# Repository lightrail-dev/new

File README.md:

# LightRail AI Compute Node — LR-P3A Rev 6.3

**Project:** LightRail AI Compute Node (Dual-CPO, NCE + HBM4 co-packaged, 1.6 Tbps photonic I/O)
**Model:** LR-P3A
**Revision:** 6.3 (32-layer HDI, IPC-6012 Class 3, 1000 A PDN — fully routed)
**Date:** 2026-05-18
**Company:** LightRail AI

> ## Rev 6.3 — Routing Complete, Fab Package Ready
>
> This revision completes the transition from Rev 6.0 scaffold to a fully
> routed 32-layer HDI PCB with the 420 × 350 mm server-class outline.
> All four interactive routing tasks have been executed:
>
> 1. **Decoupling cap fanout** — 138 nets (69 per NCE) with tiered PDN
>    (01005 → 0402 → 0805 → tantalum) and per-pad escape vias to In7/In8.
> 2. **DrMOS vertical power-tap stitching** — 6×6 via array (36 vias,
>    0.4 mm drill) per B.Cu phase, 24 phases per NCE.
> 3. **High-speed length matching** — PCIe Gen 6 ±0.15 mm, SerDes 100G
>    PAM4 ±0.15 mm, HBM4 REFCK ±0.3 mm, TFLN RF routed.
> 4. **Back-drill definitions** — all high-speed through-vias annotated
>    with residual stub ≤ 0.127 mm (5 mil).
>
> See [`docs/Tapeout_Checklist.md`](docs/Tapeout_Checklist.md) and
> [`docs/SI_PI_Thermal_Plan.md`](docs/SI_PI_Thermal_Plan.md) for remaining
> SI/PI/thermal simulation work before first-article release.

---

## 1. What's in this repo

| Path                                        | Purpose                                                              |
| ------------------------------------------- | -------------------------------------------------------------------- |
| `LightRail_LPO_1.6T.kicad_pro`              | KiCad 8 project: net classes, DRC rules, 32-layer HDI stackup.       |
| `LightRail_LPO_1.6T.kicad_sch`              | Root schematic with hierarchical sheet instances.                    |
| `LightRail_LPO_1.6T.kicad_pcb`              | Fully routed 32-layer PCB (420×350 mm, Rev 6.3).                     |
| `AI_Core.kicad_sch`                         | AI SoC + TFLN periphery + PCIe Gen6 x16 + local decoupling.          |
| `Memory.kicad_sch`                          | HBM4 stack template (side-channel + power), 8 instances per board.   |
| `VRM.kicad_sch`                             | ISL69260 + 24× ISL99390 DrMOS, V_core 0.8 V @ 1000 A+.               |
| `LightRail.pretty/`                         | Custom footprints (BGA-2500, TFLN PIC, DrMOS, HBM4_Stack_11x11mm).   |
| `docs/Architecture.md`                      | System block diagram, functional spec, interconnect budget.          |
| `docs/Stackup.md`                           | Layer stackup + controlled-impedance table (50 Ω SE / 85 Ω / 100 Ω). |
| `docs/Pinouts.md`                           | Pinout tables for SoC, TFLN PIC, PCIe x16, HBM4 stack, NVMe, MPO-24. |
| `docs/DFM_Checklist.md`                     | DFM/DFA rules (min trace, min via, BGA breakout, courtyard, etc.).   |
| `docs/Fab_Notes.md`                         | Fabrication notes: copper weights, finish, impedance tolerance.      |
| `docs/Tapeout_Checklist.md`                 | Pre-tapeout sign-off items grouped by owner.                         |
| `docs/SI_PI_Thermal_Plan.md`                | Simulation scope: SI for PCIe/HBM4-SC/TFLN, PI for V_core, thermal.  |
| `fab/BOM.csv`                               | Bill of materials down to 0201 passives.                             |
| `fab/Netlist.md`                            | Summary of representative nets (full KiCad netlist exported locally).|
| `fab/export_gerbers.sh`                     | `kicad-cli` script to export Gerbers, drills, IPC-D-356, BOM, pos.   |
| `fab/drc_custom.kicad_dru`                  | Custom DRC rules (coupled diff-pair, BGA breakout, high-current).    |
| `fab/gerber_layers.txt`                     | Layer → Gerber file mapping for the fab.                             |

---

## 2. Architectural summary

| Subsystem        | Spec                                                                             |
| ---------------- | -------------------------------------------------------------------------------- |
| Compute          | 2× composite BGA-2500 module (NCE die + silicon interposer + 4× HBM4 stacks)    |
| Photonics        | 2× TFLN modulator array (8 ch × 200 Gbps PAM4 each = 1.6 Tbps aggregate)         |
| Lasers           | 1550 nm DFB × 8 per optical engine, TEC-controlled                               |
| Memory           | 8× HBM4 12-Hi stacks (4 per module) co-packaged on silicon interposer —         |
|                  | 1024-lane data bus routes inside the interposer, never on PCB                    |
| PCIe             | PCIe Gen 6.0 x16 (32 GT/s per lane, 128 GB/s per direction)                      |
| NVMe             | M.2 / U.3 PCIe Gen 5/6 storage (via root complex)                                |
| Power            | 2× 24-phase DrMOS VRM (ISL69260 + ISL99390) for V_core 0.8 V @ 1000 A+ per unit  |
| Aux rails        | 12 V input → 3.3 V, 1.8 V, 1.2 V, 1.05 V, 0.9 V (LDO + buck)                     |
| Mgmt             | EC/BMC, PMBus, I²C, SPI flash (UEFI/BIOS), TPM 2.0 header                        |
| Front panel      | MPO-24 optical (1.6 Tbps), status LEDs                                           |
| Cooling          | Direct-to-chip cold plate headers (compute units), forced-air baseline           |
| Stackup          | **32-layer HDI** — Megtron-7 signal + high-Tg FR-4 plane + Faradflex BC24 embedded-cap core. See [`docs/Stackup.md`](docs/Stackup.md). |
| Board class      | **IPC-6012 Class 3** (aspect ratio ≤ 12:1, back-drill stub ≤ 5 mil, min hole-wall 20 µm). |
| Board outline    | 420 × 350 mm server-class (Rev 6.3, expanded from HHHL scaffold)     |

See [`docs/Architecture.md`](docs/Architecture.md) for the block diagram and
signal-flow description.

---

## 3. Net classes (KiCad project)

| Net class        | Width   | Diff gap | Clear. | Via drill / dia | Intended use                     |
| ---------------- | ------- | -------- | ------ | --------------- | -------------------------------- |
| `SERDES_100G_PAM4` | 0.09 mm | 0.09 mm  | 0.127 mm | 0.15 / 0.30 mm  | PCIe lanes, internal 100G SerDes |
| `PCIe_Gen6`      | 0.12 mm | 0.18 mm  | 0.12 mm  | 0.15 / 0.35 mm  | PCIe Gen 6 edge + retimer        |
| `TFLN_RF`        | 0.15 mm | 0.20 mm  | 0.15 mm  | 0.10 / 0.30 mm  | TFLN modulator RF drive          |
| `RF_50OHM_DIFF`  | 0.10 mm | 0.10 mm  | 0.15 mm  | 0.15 / 0.30 mm  | 50 Ω diff (clock distribution)   |
| `HBM4_Interposer`| 0.10 mm | 0.15 mm  | 0.10 mm  | 0.15 / 0.30 mm  | HBM4 side-channel (REFCK, JTAG)  |
| `TFLN_ELEC_TRANSITION` | 0.09 mm | 0.127 mm | 0.10 mm | 0.15 / 0.30 mm | TFLN RF → PIC electrical transition (< 5 mm, 50 Ω SE / 100 Ω diff) |
| `PDN_BYPASS`     | 0.20 mm | —        | 0.10 mm  | 0.15 / 0.30 mm  | Tier-3/Tier-4 decoupling escape  |
| `I2C_SPI`        | 0.15 mm | —        | 0.15 mm  | 0.20 / 0.40 mm  | Low-speed mgmt                   |
| `PWR_12V`        | 1.00 mm | —        | 0.20 mm  | 0.40 / 0.80 mm  | 12 V bulk                        |
| `PWR_3V3`        | 0.50 mm | —        | 0.15 mm  | 0.30 / 0.60 mm  | 3.3 V                            |
| `PWR_1V8`        | 0.30 mm | —        | 0.15 mm  | 0.25 / 0.50 mm  | 1.8 V                            |
| `PWR_CORE`       | 2.00 mm | —        | 0.40 mm  | 0.60 / 1.20 mm  | V_core 0.8 V @ 1000 A (plane-preferred, vertical delivery) |

See [`docs/Stackup.md`](docs/Stackup.md) for the impedance target for each net
class against the assumed dielectric stackup.

---

## 4. Design rules (project DRC) — IPC-6012 Class 3

- Minimum trace: **0.075 mm** (3 mil)
- Minimum via annular ring: **0.05 mm** (Class 3 etch/plate tolerance)
- Minimum via diameter: **0.30 mm**, drill **0.15 mm**
- **Through-via drill ≥ 0.30 mm** on a 3.48 mm board keeps aspect ratio ≤ 11.6 : 1 (spec §II: ≤12:1)
- **Back-drill residual stub ≤ 0.127 mm (5 mil)** on all high-speed classes (see `docs/Stackup.md` §4)
- Microvias: allowed, 0.20 mm diameter / 0.10 mm drill (laser-drilled HDI)
- Blind/buried vias: allowed
- Copper-to-edge (RF classes): **2.54 mm (100 mil)** per spec §V
- Copper-to-edge (general): **0.50 mm**
- Hole-to-hole: **0.15 mm**
- Min hole-wall copper: **20 µm** (IPC-6012 Class 3, pulse-plate)
- Acid-trap avoidance: ≥ **6 mil** at 3-way junctions or curved routing (spec §V)
- Solder-mask expansion: ≥ **2 mil** per side (spec §V)
- Minimum silk text: **0.80 mm** tall, 0.08 mm stroke; no silk over copper

Additional domain rules are encoded in
[`fab/drc_custom.kicad_dru`](fab/drc_custom.kicad_dru) — 7 rule groups
covering PDN integrity, high-speed diff-pair coupling, HBM4 side-channel,
HDI via/aspect, optical keep-outs, thermal via arrays, and DFM.

---

## 5. Known limitations & remaining work

1. ~~**Board outline is PCIe HHHL-derived (168 × 100 mm).**~~ — **resolved
   in Rev 6.3**: outline expanded to 420 × 350 mm server-class with M3
   corner + cold-plate bolster mounting holes.
2. ~~**No trace routing.**~~ — **resolved in Rev 6.3**: decoupling fanout
   (138 nets), DrMOS stitching (6×6 via array per phase), PCIe Gen 6 /
   SerDes 100G PAM4 / HBM4 REFCK / TFLN RF length-matched routing, and
   back-drill definitions are all implemented.
3. **Pad-to-net assignments remain schematic-side.** The PCB-side net
   assignments generated by the Rev 6.3 script are representative; a
   schematic-ECO pass against vendor composite-module datasheets is still
   required for final ERC/DRC clean.
4. **HBM4 interposer is vendor-delegated.** The HBM4 1024-lane data bus is
   routed inside the vendor-supplied silicon interposer (TSMC CoWoS-L /
   Intel Foveros-S class) co-packaged with the NCE. The PCB only escapes the
   composite module's side-channel signals (REFCK, CATTRIP, PWR_GOOD,
   IEEE-1500 JTAG) and power rails. HBM4 stack footprints are DNP
   documentation placeholders.
5. **No SI/PI/thermal simulation.** Impedance targets are *design intents*, not
   measured values. 1000 A V_core needs PDN decoupling sweep + IR-drop + thermal
   co-sim. TFLN RF needs full-wave EM simulation. See
   `docs/SI_PI_Thermal_Plan.md`.
6. **TFLN modulator and PCIe Gen 6 retimer IP is vendor-NDA.** The footprints
   and symbols here are placeholders with plausible pin counts; real parts will
   need vendor datasheets and reference designs.
7. **Gerbers not checked in.** Use [`fab/export_gerbers.sh`](fab/export_gerbers.sh)
   to generate the full fab package (ODB++, Gerber X2, Excellon, IPC-D-356A,
   PnP, BOM, 3D STEP).

---

## 6. How to open

```bash
# Requires KiCad 8.0 or later.
kicad LightRail_LPO_1.6T.kicad_pro
```

First-time recommended actions in the GUI:

1. **Schematic:** Run Inspect → Electrical Rules Checker (ERC). Expect many
   `hierarchical_label_mismatch` and `pin_not_connected` warnings — these are
   the starting work list.
2. **PCB:** Run Inspect → Design Rules Checker (DRC). Expect many
   `unconnected_items` and `missing_footprint` errors — these correspond to
   the pad-to-net gaps listed in §5.
3. Run File → Fabrication Outputs → Gerbers with the layer selection in
   [`fab/gerber_layers.txt`](fab/gerber_layers.txt).

---

## 7. Exporting fab outputs

Once the design passes ERC/DRC in KiCad:

```bash
cd fab && ./export_gerbers.sh
```

This produces:

- `fab/gerbers/*.gbr` (one per copper + mask + silk + paste + edge layer)
- `fab/gerbers/*.drl` (PTH + NPTH drill files, Excellon 2)
- `fab/LightRail_LPO_1.6T.ipc-d-356` (IPC-D-356A netlist for bare-board test)
- `fab/LightRail_LPO_1.6T.pos` (pick-and-place CSV, top + bottom)
- `fab/LightRail_LPO_1.6T.bom.csv` (BOM exported from the schematic — cross-check against `fab/BOM.csv`)
- `fab/LightRail_LPO_1.6T.step` (3D STEP model, for mechanical fit)

---

## 8. Revision history

| Rev  | Date       | Change                                                                   |
| ---- | ---------- | ------------------------------------------------------------------------ |
| 1.0  | 2026-04-10 | Initial LPO 1.6T photonic accelerator scaffold (PR #1).                  |
| 2.0  | 2026-04-11 | DRC-violation sweep (PR #2, not merged).                                 |
| 3.0  | 2026-04-11 | Dual AI Compute Node scaffold with TFLN, VRM, DDR5 hierarchy (PR #4).    |
| 4.0  | 2026-04-17 | Add fab documentation package: BOM, pinouts, stackup, DFM, tapeout list. |
| 4.1  | 2026-04-17 | Stackup / PCB fixes from Devin Review: V_CORE_U1 planes 2 oz (matches zones), DDR5 CK moved In1.Cu→In2.Cu with P/N endpoints matched, TFLN keep-outs moved off BGA to front-panel fiber-exit area (both F.Cu and B.Cu), DDR5_Data via_diameter 0.3→0.35 mm, `ddr5_ca_stripline_only` DRC rule uses regex on full net names (`.*_CK_P` etc.), `gerber_layers.txt` In5/In6 re-labelled V_CORE_U1. |
| 4.2  | 2026-04-17 | Scaffold parse-fix + fab export: stripped `;;` line comments and property `(id N)` tokens from `.kicad_pcb` so `kicad-cli` parses; `fab/export_gerbers.sh` no longer aborts on DRC violations; `ddr5_ck_ca_length_match` DRC rule keys off `DDR5_Data` net class + NetName regex (old `DDR5_CK`/`DDR5_CA` classes never existed); `Memory.kicad_sch` instances carry `VDDQ` sheet pin; `AI_Core_Unit[01]` sheet instances + `AI_Core.kicad_sch` now carry `VDDQ` hierarchical pin/label (SoC DDR5 I/O rail); `fab/generate_bom.py` ref-des reconciled with PCB (`U101/U201` SoCs, `U102/U202` TFLN, `U302..U349` DrMOS — was colliding with SoCs). |
| 5.0  | 2026-04-17 | **Memory-subsystem migration: DDR5-8800 → HBM4 co-packaged on silicon interposer.** Removed 8× DDR5 DIMM footprints (4 per unit) and the fly-by topology; composite NCE+HBM4 module (4× HBM4 12-Hi stacks per unit on vendor-supplied interposer) placed flanking each NCE. PCB nets 148–163 renamed `DDR5_U{0,1}_*` → `HBM4_U{0,1}_*`; net class `DDR5_Data` → `HBM4_Interposer`. DRC rules rewritten for HBM4 side-channel (REFCK 100 Ω diff, IEEE-1500 50 Ω SE, length 5–35 mm). `Memory.kicad_sch` rewritten as HBM4 stack template (9 external pins + IEEE-1500). Docs (Architecture, Stackup, Pinouts, Fab_Notes, SI/PI/Thermal, Tapeout, DFM, README) updated for interposer topology. HBM4 1024-lane data bus is interposer-internal and explicitly not PCB-routed. |
| 6.0  | 2026-04-19 | **32-layer HDI physical synthesis (spec §I–§V).** Stackup expanded 10 → 32 layers: Megtron-7 signal (εr=3.3) + high-Tg FR-4 plane (εr=4.2) + Faradflex BC24 embedded-capacitance core (εr=14). P/G plane-pair spacing = 3 mil (< 5 mil target). Symmetric construction (mirror about In15–In16) for warpage control. `PWR_CORE` net-class via diameter/drill 0.8/0.4 → 1.2/0.6 mm and clearance 0.3 → 0.4 mm for 1000 A PDN. Two new net classes added: `PDN_BYPASS` (Tier-3/Tier-4 decoupling) and `TFLN_ELEC_TRANSITION` (< 5 mm F.Cu microstrip for RF→PIC transition). DRC rewritten: IPC-6012 Class 3 aspect ratio (≤12:1 via 0.30 mm min through drill), back-drill stub ≤ 0.127 mm, 20 µm hole-wall copper, 100 mil RF edge clearance, acid-trap / mask-expansion / silk-over-copper checks, HBM4 REFCK stripline-only, TFLN optical keep-outs on every inner layer, thermal via array ≤ 1 mm blind vias, length-matching tightened to ≤ 2 ps. `fab/generate_bom.py` adds tiered PDN: 24 × 100 µF tantalum + 160 × 10 µF 0805 + 400 × 1 µF 0402 + 1120 × 100 nF 01005 + thermal-via-array entries (TV1/TV2). `fab/export_gerbers.sh` exports all 32 copper layers + ODB++ as primary fab transfer + IPC-2581C/IPC-D-356A redundant. `fab/gerber_layers.txt` updated for 32-layer map + per-span drills + back-drill depth table. |
| 6.3  | 2026-05-18 | **Rev 6.3: Full routing & fab-ready PCB.** Board outline expanded from 168×100 mm HHHL scaffold to 420×350 mm server-class. Component floorplan implemented: NCE A/B at (135,160)/(285,160), TFLN PIC A/B at (185,160)/(235,160), 24-phase DrMOS in 4 clusters (left/right columns F.Cu + bottom rows B.Cu under NCE). 138-net tiered decoupling fanout (36× 01005 100nF + 18× 0402 1µF + 9× 0805 10µF + 6× tantalum 100µF per NCE) with escape vias to In7/In8. DrMOS vertical power-tap stitching: 6×6 via array (0.4mm drill, 1.0mm pitch) per B.Cu phase. Length-matched high-speed routing: PCIe Gen6 x16 on In5/In26 (±0.15mm), SerDes 100G PAM4 on In3/In28 (±0.15mm), HBM4 REFCK on In2/In29 (±0.3mm), TFLN RF on In7/In24. Back-drill definitions on all high-speed through-vias (stub ≤0.127mm). Optical keep-out zones on all 32 copper layers. Power/GND zones on inner planes. 64× QSFP-DD on west edge, PCIe CEM x16 on south edge. `scripts/generate_rev63.py` added as reproducible PCB generator. |

### Residual items flagged by Devin Review that still require human work

These are schematic-side fixes that need a PCB engineer to drive in the KiCad
GUI (a text-edit pass risks corrupting sheet-pin UUIDs):

- `AI_Core_Unit[01]` sheet instances in root schematic carry the HBM4
  side-channel pins (`HBM4_U*_VDDC_S / VDDQL_S / VDDQ_S / VPP_S / REFCK_P /
  REFCK_N / CATTRIP / PWR_GOOD`), `VDDQ`, and the IEEE-1500 test-bus pins
  (`HBM4_IEEE_TCK / TMS / TDI / TDO`); matching hierarchical labels are in
  `AI_Core.kicad_sch`. A PCB engineer should verify the composite-BGA
  power-pin count against the vendor composite-module datasheet once the
  NCE + interposer vendor is selected.
- ~~`VRM_U[01]` sheet instances are missing `VID0/1/2` input pins~~ —
  **resolved**: VID0/1/2 pins are present on both `VRM_Unit0` and
  `VRM_Unit1` sheet instances and matched by hierarchical labels in
  `VRM.kicad_sch`.
- ~~TFLN keep-out polygons on inner copper layers (`In1.Cu`..`In8.Cu`) should
  be added once final placement is locked~~ — **resolved in Rev 6.3**:
  optical keep-out zones now declared on all 32 copper layers around each
  TFLN edge coupler and the central photonic bridge.

---

## 9. License & contact

This design is proprietary to LightRail AI. Contact `pcb-engineering@lightrail.ai`
for review, fabrication quotes, or sim sign-off.

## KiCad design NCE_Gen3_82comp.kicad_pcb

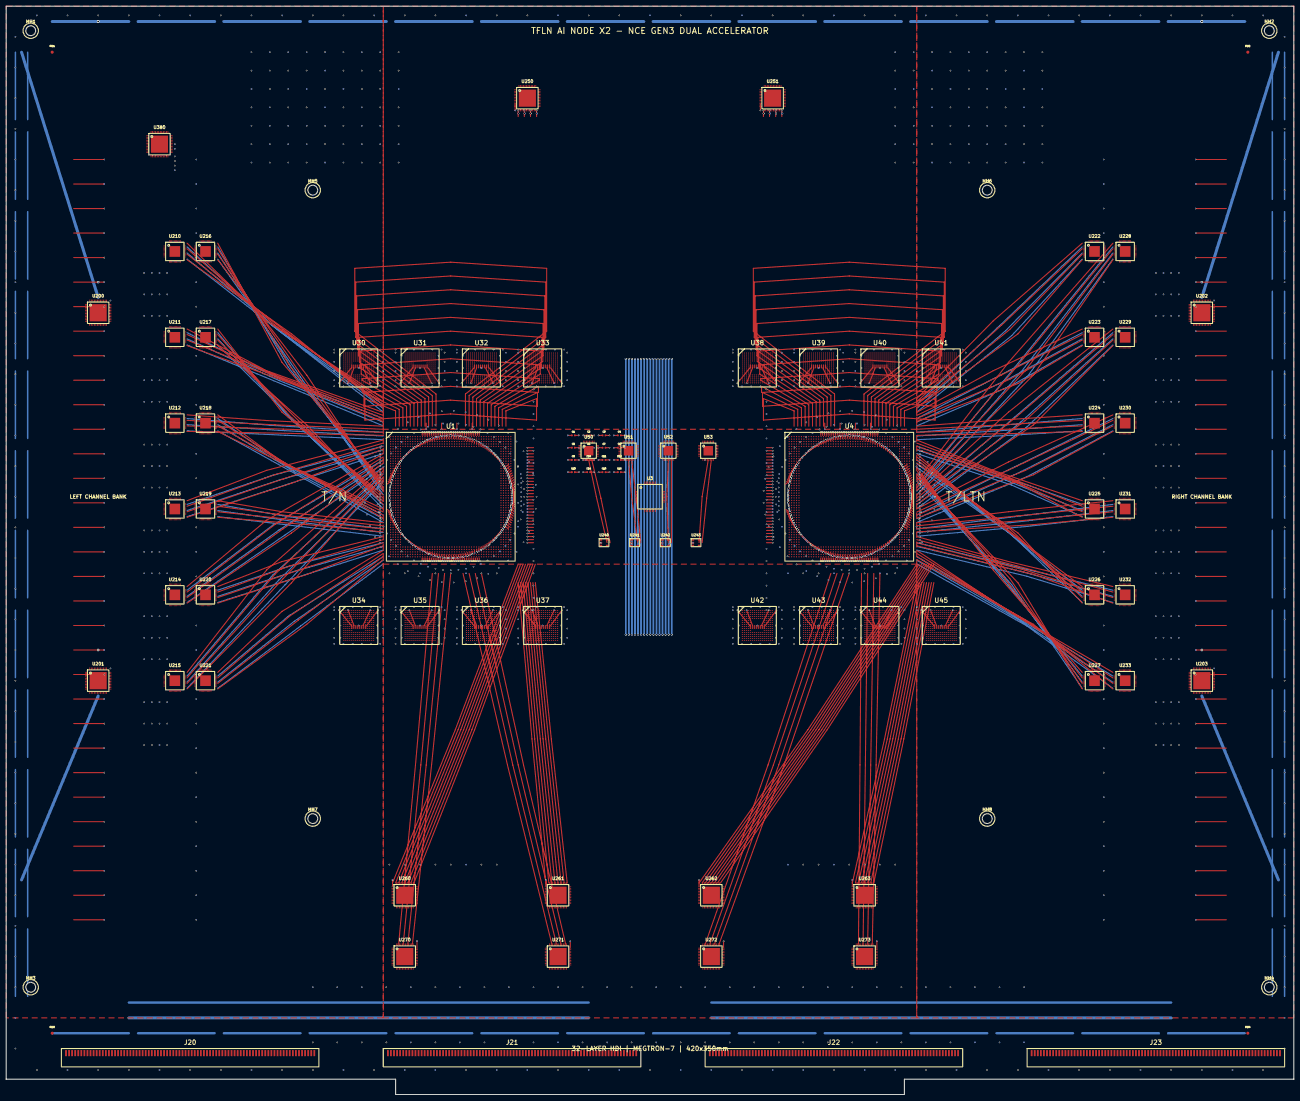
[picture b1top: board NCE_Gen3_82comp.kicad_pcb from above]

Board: 32 copper layers, 420.0 x 355.0 mm, 98 parts (0 on the bottom side), 5 nets.

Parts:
C1, C2, C3, C4, C5, C6, C7, C8, C9, C10, C11, C12, C13, C14, C15, C16: 100nF; C_0402_1005Metric
FID1, FID2, FID3, FID4: Fiducial; Fiducial_1mm_Mask2.5mm
J20, J21, J22, J23: PCIe_x16_SLOT; PCIE_x16_SLOT
MH1, MH2, MH3, MH4, MH5, MH6, MH7, MH8: MountingHole; MountingHole_3.2mm_M3
U1, U4: NCE_Gen3; NCE_BGA2500_40x40mm
U3: TFLN_PIC_4xMZM; Custom_Optical_Module_25x8mm
U30, U31, U32, U33, U34, U35, U36, U37, U38, U39, U40, U41, U42, U43, U44, U45: HBM4-16GB; BGA-1024_12x9mm
U50, U51, U52, U53: HMC8410; QFN-32-1EP_5x5mm_P0.5mm_EP3.1x3.1mm
U200, U201, U202, U203: ISL69260; QFN-48-1EP_7x7mm_P0.5mm_EP5.6x5.6mm
U210, U211, U212, U213, U214, U215, U216, U217, U218, U219, U220, U221, U222, U223, U224, U225, U226, U227, U228, U229, U230, U231, U232, U233: ISL99390; PQFN-40_5x6mm
U240, U241, U242, U243: ADP7118-0.9V; SOT-23-5
U250, U251: Si5395A; QFN-48-1EP_7x7mm_P0.5mm_EP5.6x5.6mm
U260, U261, U262, U263: BCM84881; QFN-48-1EP_7x7mm_P0.5mm_EP5.6x5.6mm
U270, U271, U272, U273: PEX88096; QFN-48-1EP_7x7mm_P0.5mm_EP5.6x5.6mm
U380: AST2600; QFN-48-1EP_7x7mm_P0.5mm_EP5.6x5.6mm

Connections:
+0V8: C1.1, C2.1, C3.1, C4.1
+0V9: C13.1, C14.1, C15.1, C16.1
+1V8: C5.1, C6.1, C7.1, C8.1
+3V3: C9.1, C10.1, C11.1, C12.1
GND: C1.2, C2.2, C3.2, C4.2, C5.2, C6.2, C7.2, C8.2, C9.2, C10.2, C11.2, C12.2, C13.2, C14.2, C15.2, C16.2

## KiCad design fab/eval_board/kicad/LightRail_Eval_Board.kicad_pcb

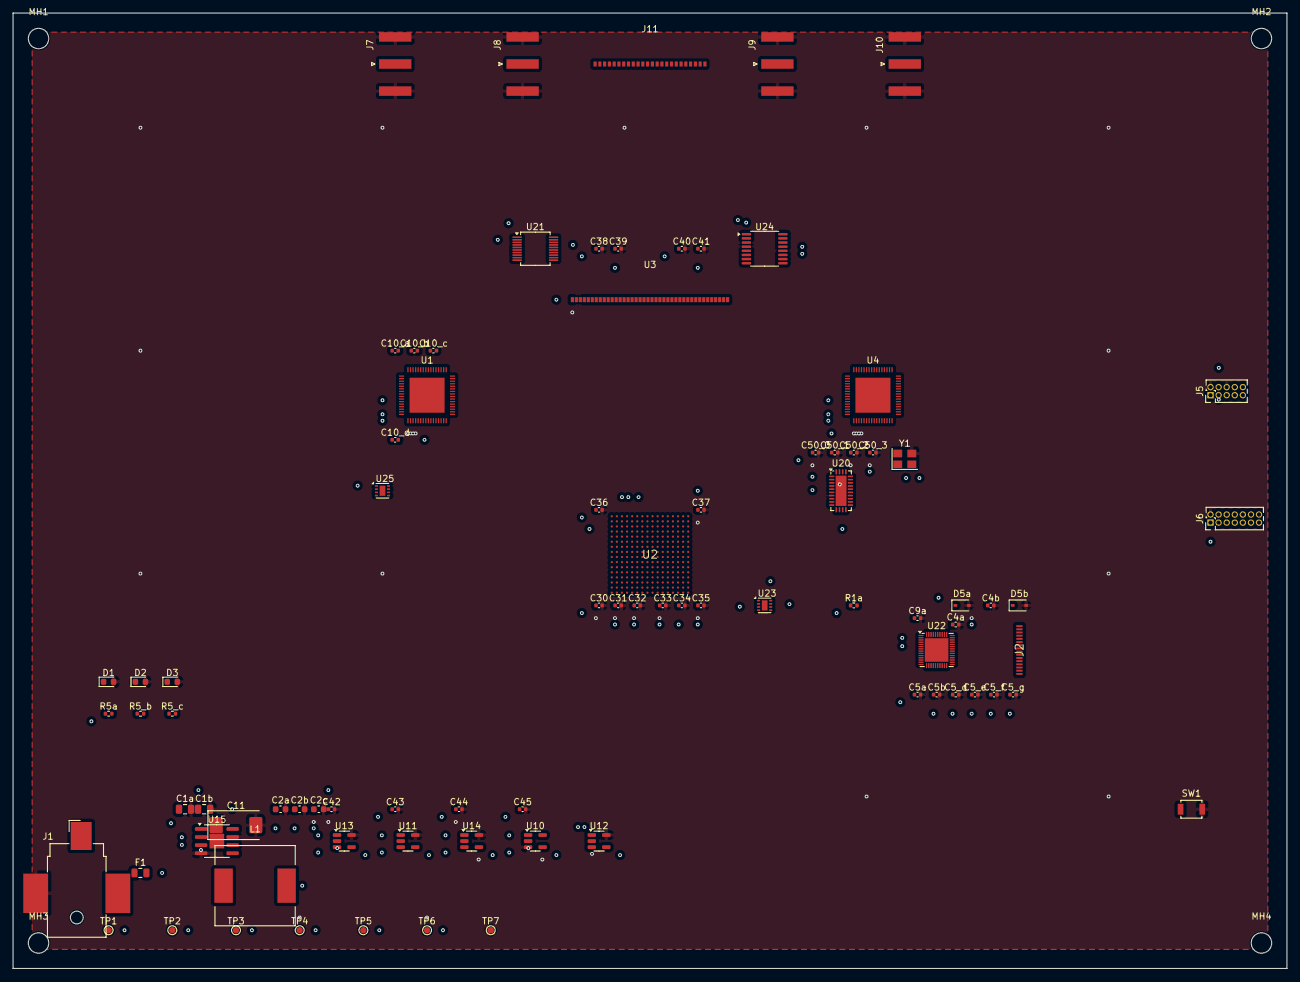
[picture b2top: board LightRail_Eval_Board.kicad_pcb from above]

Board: 22 copper layers, 200.0 x 150.0 mm, 88 parts (0 on the bottom side), 82 nets, no tracks yet.

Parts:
C1a, C1b: 22uF; C_0805_2012Metric
C2a, C2b, C2c: 10uF; C_0603_1608Metric
C4a, C4b: 1uF; C_0402_1005Metric
C5_d, C5_e, C5_f, C5_g, C5a, C5b, C9a, C10_a, C10_b, C10_c, C10_d, C30, C31, C32, C33, C34, C35, C36, C37, C42, C43, C44, C45, C50_0, C50_1, C50_2, C50_3: 100nF; C_0402_1005Metric
C11: 100uF; CP_EIA-7343-15_Kemet-W
C38, C39, C40, C41: 4.7uF; C_0402_1005Metric
D1: Green; LED_0603_1608Metric
D2: Blue; LED_0603_1608Metric
D3: Red; LED_0603_1608Metric
D5a, D5b: PRTR5V0U2X; D_SOD-323
F1: 2A; Fuse_0805_2012Metric
J1: DC_12V; BarrelJack_CUI_PJ-036AH-SMT_Horizontal
J2: USB-C; USB_C_Numeric
J5: JTAG; PinHeader_2x05_P1.27mm_Vertical
J6: GPIO; PinHeader_2x07_P1.27mm_Vertical
J7, J8, J9, J10: SMA; SMA_Amphenol_132289_EdgeMount
J11: MPO-24
L1: 4.7uH; L_12x12mm_H4.5mm
MH1, MH2, MH3, MH4: M3; MountingHole_3.2mm_M3
R1a: 10k; R_0402_1005Metric
R5_b, R5_c, R5a: 330; R_0402_1005Metric
SW1: RESET; SW_SPST_B3U-1000P
TP1: +12V; TestPoint_Pad_D1.0mm
TP2: +5V; TestPoint_Pad_D1.0mm
TP3: +3V3; TestPoint_Pad_D1.0mm
TP4: +1V8; TestPoint_Pad_D1.0mm
TP5: +1V0; TestPoint_Pad_D1.0mm
TP6: +0V9; TestPoint_Pad_D1.0mm
TP7: GND; TestPoint_Pad_D1.0mm
U1: NCE_TEST_CHIP; QFN-64_8x8mm_P0.4mm
U2: XC7A100T; BGA-256_Numeric
U3: TFLN_PIC; Custom_Optical_Module
U4: NCE_TEST_CHIP_B; QFN-64_8x8mm_P0.4mm
U10: ADP7118; TSOT-23-5
U11, U14: TPS7A2018; SOT-23-5
U12: TPS7A2010; SOT-23-5
U13: TPS7A3301; SOT-23-5
U15: TPS54360; HSOP-8-1EP_3.9x4.9mm_P1.27mm_EP2.3x2.3mm
U20: Si5395A; QFN-28-1EP_3x6mm_P0.5mm_EP1.7x4.75mm
U21: AD7928; TSSOP-20_4.4x5mm_P0.4mm
U22: FT232H; QFN-48-1EP_5x5mm_P0.35mm_EP3.7x3.7mm
U23: W25Q128JVS; WSON-8-1EP_2x2mm_P0.5mm_EP0.9x1.6mm
U24: AD5684R; TSSOP-16_4.4x5mm_P0.65mm
U25: TMP461; WSON-8-1EP_2x2mm_P0.5mm_EP0.9x1.6mm
Y1: 100MHz; Crystal_SMD_3225-4Pin_3.2x2.5mm

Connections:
+0V9: C4b.1, C30.1, C31.1, C32.1, C33.1, TP6.1, U1.1, U1.2, U1.63, U4.1, U4.2, U4.63, U10.4
+1V0: C4a.1, C38.1, C39.1, C40.1, C41.1, TP5.1, U2.1, U2.2, U12.4
+1V8: C2b.1, C2c.1, C5b.1, C34.1, C35.1, C36.1, C37.1, C42.1, C43.1, C44.1, C45.1, C50_0.1, C50_1.1, C50_2.1, C50_3.1, TP4.1, U1.3, U1.4, U1.64, U2.3, U2.4, U3.1, U4.3, U4.4, U4.64, U10.1, U10.2, U11.4, U12.1, U12.2, U14.4, U20.2, U20.25, U20.26, U20.27
+3V3: C2a.1, C5_d.1, C5_e.1, C5_f.1, C5_g.1, C5a.1, J5.4, J6.1, R1a.1, R5a.1, TP3.1, U11.1, U11.2, U13.4, U14.1, U14.2, U20.1, U20.13, U21.1, U21.2, U21.17, U22.1, U22.2, U23.3, U23.7, U23.8, U24.1, U24.2, U24.13, U24.14, U25.1, Y1.1, Y1.2
+5V: C1b.1, L1.2, TP2.1, U13.1, U13.2
+12V: C1a.1, C11.1, F1.2, TP1.1, U15.2, U15.3
+12V_RAW: F1.1, J1.1
AXI_ACLK: U1.9, U2.9
AXI_ARESETN: U1.10, U2.10
AXI_AWADDR: U1.11, U2.11
AXI_AWVALID: U1.12, U2.12
AXI_RDATA: U1.22, U2.15
AXI_RVALID: U1.23, U2.16
AXI_WDATA: U1.14, U2.13
AXI_WVALID: U1.15, U2.14
CLK_100M: U20.5, Y1.4
CLK_CORE: U1.24, U2.25, U4.24, U20.15
CLK_REF: U1.25, U2.26, U4.25, U20.17
DAC_V1: U3.12, U24.5
DAC_V2: U3.13, U24.6
DAC_V3: U3.14, U24.7
DAC_V4: U3.15, U24.8
FLASH_CS: U2.20, U23.1
FLASH_MISO: U2.18, U23.2
FLASH_MOSI: U2.17, U23.5
FLASH_SCK: U2.19, U23.6
FPGA_GPIO0: J6.3, U2.29
FPGA_GPIO1: J6.4, U2.30
FPGA_GPIO2: J6.5, U2.31
FPGA_GPIO3: J6.6, U2.32
FT_RXLED: R5_c.1, U22.23
FT_TXLED: R5_b.1, U22.22
GND: C1a.2, C1b.2, C2a.2, C2b.2, C2c.2, C4a.2, C4b.2, C5_d.2, C5_e.2, C5_f.2, C5_g.2, C5a.2, C5b.2, C9a.2, C11.2, C30.2, C31.2, C32.2, C33.2, C34.2, C35.2, C36.2, C37.2, C38.2, C39.2, C40.2, C41.2, C42.2, C43.2, C44.2, C45.2, C50_0.2, C50_1.2, C50_2.2, C50_3.2, D1.2, D2.2, D3.2, D5a.2, D5b.2, J1.2, J2.8, J2.9, J5.2, J5.6, J6.2, J7.2, J8.2, J9.2, J10.2, SW1.2, TP7.1, U1.5, U1.6, U1.7, U1.8, U1.61, U1.62, U2.5, U2.6, U2.7, U2.8, U3.2, U3.3, U4.5, U4.6, U4.7, U4.8, U4.61, U4.62, U10.3, U11.5, U12.5, U13.5, U14.5, U15.4, U15.7, U20.3, U20.4, U20.6, U20.7, U20.8, U20.28, U21.3, U21.4, U21.18, U22.3, U22.4, U23.4, U24.3, U24.4, U24.12, U25.2, U25.6, U25.8, Y1.3
I2C_SCL: J6.13, U1.49, U4.49, U20.10, U25.4
I2C_SDA: J6.14, U1.50, U4.50, U20.9, U25.3
JTAG_TCK: J5.1, U1.26, U2.21
JTAG_TDI: J5.9, U1.28, U2.23
JTAG_TDO: J5.3, U1.29, U2.24
JTAG_TMS: J5.5, U1.27, U2.22
LED_A: D1.1, R5a.2
LED_D2: D2.1, R5_b.2
LED_D3: D3.1, R5_c.2
MON_CH0: U3.25, U21.5
MON_CH1: U3.26, U21.6
MON_CH2: U3.27, U21.7
MON_CH3: U3.28, U21.8
MON_CH4: U3.29, U21.9
MON_CH5: U3.30, U21.10
MON_CH6: U3.31, U21.11
MON_CH7: U3.32, U21.12
OPT_RX0: J11.5, U3.21
OPT_RX1: J11.6, U3.22
OPT_RX2: J11.7, U3.23
OPT_RX3: J11.8, U3.24
OPT_TX0: J11.1, U3.17
OPT_TX1: J11.2, U3.18
OPT_TX2: J11.3, U3.19
OPT_TX3: J11.4, U3.20
PLL_LOL: U20.12, U20.14
RESET_N: C9a.1, R1a.2, SW1.1, U1.60, U4.60, U20.11, U22.7
SMA_J7: C10_a.2, J7.1
SMA_J8: C10_b.2, J8.1
SMA_J9: C10_c.2, J9.1
SMA_J10: C10_d.2, J10.1
SPI_CLK: U1.30, U4.30, U21.13, U24.9
SPI_MISO: U1.32, U21.15
SPI_MOSI: U1.31, U21.14, U24.11
SW_5V: L1.1, U15.8
TEMP_ALERT: U1.57, U25.5
TEMP_DIODE: U3.16, U25.7
TFLN_TX_N0: C10_b.1, U1.34, U3.5
TFLN_TX_N1: C10_d.1, U1.36, U3.7
TFLN_TX_N2: U1.38, U3.9
TFLN_TX_N3: U1.40, U3.11
TFLN_TX_P0: C10_a.1, U1.33, U3.4
TFLN_TX_P1: C10_c.1, U1.35, U3.6
TFLN_TX_P2: U1.37, U3.8
TFLN_TX_P3: U1.39, U3.10
UART_RX: U1.52, U2.28, U22.14
UART_TX: U1.51, U2.27, U22.13
USB_DN: D5b.1, J2.5, U22.6
USB_DP: D5a.1, J2.4, U22.5

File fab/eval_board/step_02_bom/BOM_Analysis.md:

# Step 2: BOM — Bill of Materials Analysis
## LightRail NCE+TFLN Evaluation Board (100×100 mm)

**Date:** 2026-05-26
**Revision:** 1.0

---

## 1. BOM Summary

| Metric | Value |
|--------|-------|
| **Total part instances** | 183 |
| **Unique line items** | 62 |
| **SMD parts (top)** | 168 |
| **SMD parts (bottom)** | 8 |
| **Through-hole parts** | 7 |
| **Board assembly sides** | 2 (top primary, bottom decoupling only) |

## 2. Package Distribution

| Package | Qty | Notes |
|---------|-----|-------|
| 0402 | 72 | Bypass caps, pull-up/pull-down resistors |
| 0603 | 18 | Power path caps, LED series resistors |
| 0805 | 8 | Bulk decoupling, power input caps |
| QFN-64 (8×8 mm) | 1 | NCE test chip U1 |
| BGA-256 (14×14 mm) | 1 | Xilinx Artix-7 XC7A100T U2 |
| Custom optical module | 1 | TFLN PIC U3 |
| SOT-23-5 | 6 | LDO regulators |
| D-PAK / SOT-223 | 2 | 5V buck, power MOSFETs |
| QFN-48 (7×7 mm) | 1 | FT232H USB-UART bridge |
| QFN-28 (5×5 mm) | 1 | Si5395A PLL |
| 3.2×2.5 mm | 1 | 100 MHz TCXO |
| SMA edge-mount | 4 | RF probe connectors |
| USB-C SMT | 1 | USB interface |
| 2×5 1.27mm header | 1 | JTAG |
| 2×7 1.27mm header | 1 | GPIO expansion |
| Barrel jack | 1 | 12V power input |
| 2-pin power header | 1 | Alternative 12V input |
| M.2 Key-M | 0 | Not on eval board |
| Test point (0.8mm pad) | 16 | Power rail + signal TPs |

## 3. Key Components

### 3.1 Active ICs

| Ref | Part | MPN | Package | Function |
|-----|------|-----|---------|----------|
| U1 | NCE Test Chip | LR-NCE-MPW-001 | QFN-64 | DUT — Neural Compute Engine |
| U2 | Artix-7 FPGA | XC7A100T-1FTG256C | BGA-256 | AXI master, test controller |
| U3 | TFLN PIC | LR-TFLN-PIC-001 | Custom | Optical transceiver module |
| U10 | LDO 0.9V | ADP7118AUJZ-0.9-R7 | TSOT-5 | NCE VDD_CORE |
| U11 | LDO 1.8V | TPS7A2018DBVR | SOT-23-5 | NCE VDD_IO |
| U12 | LDO 1.0V | TPS7A2010DBVR | SOT-23-5 | FPGA VCCINT |
| U13 | LDO 3.3V | TPS7A3301DBVR | SOT-23-5 | FPGA VCCAUX |
| U14 | LDO 1.8V | TPS7A2018DBVR | SOT-23-5 | FPGA VCCO bank |
| U15 | Buck 5V | TPS54360DDAR | HSOP-8 | Main 12V→5V converter |
| U20 | PLL | Si5395A-A-GM | QFN-28 | Clock synthesis (100 MHz, 2 GHz, 156.25 MHz) |
| U21 | ADC | AD7928BRUZ | TSSOP-20 | TFLN photodetector monitor |
| U22 | USB-UART | FT232HQ | QFN-48 | USB debug interface |
| U23 | SPI Flash | W25Q128JVSIQ | WSON-8 | FPGA configuration bitstream |
| U24 | DAC | AD5684RBRUZ | TSSOP-16 | TFLN bias control (4-ch) |
| U25 | Temp sensor | TMP461AIDR | WSON-8 | NCE die temperature (via I2C) |

### 3.2 Passive Summary

| Type | Quantity | Values |
|------|----------|--------|
| Ceramic caps (MLCC) | 98 | 100pF–22µF (0402, 0603, 0805) |
| Resistors | 42 | 0Ω–100kΩ (0402, 0603) |
| Inductors | 3 | 4.7µH (TPS54360), ferrite beads |
| Tantalum caps | 2 | 100µF/16V (input bulk) |
| Crystal / TCXO | 1 | 100 MHz TCXO (Si531) |
| LEDs | 4 | Power, Activity, Fault, Link |

## 4. Part Availability Assessment

| Component | Source | Lead Time | Risk |
|-----------|--------|-----------|------|
| XC7A100T-1FTG256C | DigiKey/Mouser | 8–12 weeks | Medium — check allocation |
| FT232HQ | DigiKey | In stock | Low |
| Si5395A-A-GM | Mouser | 6–8 weeks | Low |
| AD7928BRUZ | DigiKey | In stock | Low |
| AD5684RBRUZ | DigiKey | In stock | Low |
| ADP7118AUJZ-0.9 | DigiKey | In stock | Low |
| TPS7A2018DBVR | DigiKey | In stock | Low |
| TPS54360DDAR | DigiKey | In stock | Low |
| W25Q128JVSIQ | LCSC/DigiKey | In stock | Low |
| TMP461AIDR | DigiKey | In stock | Low |
| NCE test chip (U1) | MPW shuttle | 16–20 weeks | Custom — schedule-dependent |
| TFLN PIC (U3) | Custom fab | 12–16 weeks | Custom — vendor-dependent |

**Long-lead items:** Artix-7 FPGA (order immediately), NCE die (MPW schedule), TFLN PIC (custom).

## 5. BOM Export Formats

| Format | File | Purpose |
|--------|------|---------|
| CSV (full) | `Eval_Board_BOM.csv` | Master BOM for procurement |
| CSV (JLCPCB) | `Eval_Board_BOM_JLCPCB.csv` | JLCPCB assembly format |
| CSV (PCBWay) | `Eval_Board_BOM_PCBWay.csv` | PCBWay turnkey format |
| Markdown | This document | Human review |
